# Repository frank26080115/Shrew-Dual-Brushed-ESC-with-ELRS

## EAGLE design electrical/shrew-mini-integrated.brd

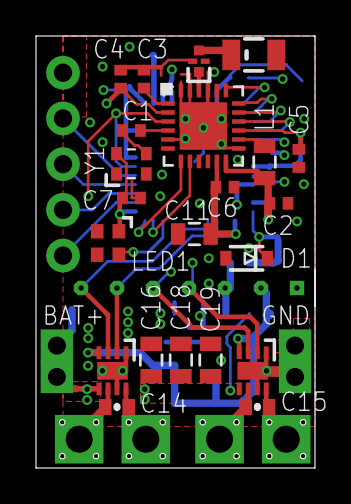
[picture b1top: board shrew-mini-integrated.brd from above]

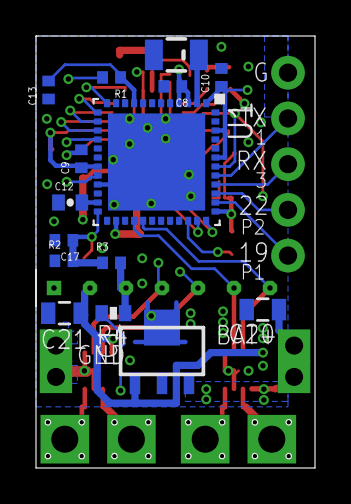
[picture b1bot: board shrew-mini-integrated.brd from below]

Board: 4 copper layers, 15.5 x 24.0 mm, 47 parts (15 on the bottom side), 35 nets.

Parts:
ANT1, ANT2: 74889302450; ANTENNA-CHIP2
C1: 1n; 0402-REV
C2, C13, C17: 470n; 0402-REV
C3, C4: 10n; 0402-REV
C5, C6, C7, C8, C9, C10: 100n; 0402-REV
C11: 10uF 25V; 0805
C12: DNP; 0402-CAP
C14, C15: 0402-CAP
C16, C18, C19, C20, C21: 0805
D1: 3V6; SOD-323
EDGE1: 1X05
FL1: 2450FM07D0034T; FIL_2450FM07D0034T
IC1: Vreg +3V3; SOT89
JP1: 1X07-2MM-TH-TINY
L1: 15u; 0805
LED1: SK6812-EC20
R1, R2, R3: 10K; 0402-REV
R4: 0402-RES
U1: ESP32-PICO-D4; PQFN50P700X700X104-49N
U2: SX1280IMLTRT; QFN24_4X4_SEM
U3, U4: DRV8231DSGR; WSON8_DRV8231_TEX
X1, X2, X3, X4: PIN-1X-BIG; PAD-1X-BIG
X5, X6, X7, X8: PIN-1X-MED; PAD-1X-MED
Y1: 52MHz TCXO; OSC_TG2016SMN_50.0000M-ECGNNMB

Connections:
3.3V: C5.2, C6.2, C7.2, C8.1, C9.1, C10.1, C11.1, C21.1, IC1.1, JP1.2, LED1.1, R1.2, U1.1, U1.3, U1.4, U1.19, U1.26, U1.37, U1.43, U1.46, U2.11, U2.15, U3.4, U4.4, Y1.4
+24V: C16.1, C18.1, C19.1, C20.1, IC1.3, R4.2, U3.5, U4.5, X5.1, X7.1
AUX1: EDGE1.1, U1.38
AUX2: EDGE1.2, U1.39
BATT-ADC: C17.1, D1.1, R2.2, R3.1, U1.24
ESP-BOOT: C12.2, U1.23
ESP-EN: C13.2, R1.1, U1.9
GND: C2.1, C3.1, C4.1, C5.1, C6.1, C7.1, C8.2, C9.2, C10.2, C11.2, C12.1, C13.1, C16.2, C17.2, C18.2, C19.2, C20.2, C21.2, D1.2, EDGE1.5, FL1.2, FL1.4, IC1.2, IC1.4, JP1.1, LED1.3, R2.1, U1.21, U1.49, U2.5, U2.13, U2.20, U2.21, U2.23, U2.24, U2.25, U3.1, U3.7, U3.9, U4.1, U4.7, U4.9, X6.1, X8.1, Y1.2
MOTOR1: C15.2, U4.6, X3.1
MOTOR2: C15.1, U4.8, X4.1
MOTOR3: C14.2, U3.6, X1.1
MOTOR4: C14.1, U3.8, X2.1
unnamed: ANT1.FEED, U1.2
unnamed: C1.1, Y1.3
unnamed: C1.2, U2.4
unnamed: FL1.1, U2.22
unnamed: ANT2.FEED, FL1.3
unnamed: L1.2, U2.14
unnamed: C3.2, U2.1
RADIO-BUSY: U1.36, U2.7
RADIO-CS: U1.12, U2.19
RADIO-DIO: U1.35, U2.8
RADIO-RST: U1.42, U2.3
RADIO-VDD: C2.2, C4.2, L1.1, U2.2, U2.12
RGBLED: LED1.4, U1.34
SIG1: JP1.4, U1.20, U4.2
SIG2: JP1.5, U1.16, U4.3
SIG3: JP1.6, U1.28, U3.2
SIG4: JP1.7, U1.29, U3.3
SPI-MISO: U1.15, U2.16
SPI-MOSI: U1.14, U2.17
SPI-SCK: U1.13, U2.18
U0RXD: EDGE1.3, U1.40
U0TXD: EDGE1.4, U1.41
V-ADC: JP1.3, R3.2, R4.1

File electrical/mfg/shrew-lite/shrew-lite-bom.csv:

Comment,Designator,Footprint,LCSC Part #
68K,R4,0402-RES,
1n,C1,0402-REV,
3V6 zener,D1,SOD-323,C306657
10K,R1 R2 R3,0402-REV,
10n,C3 C4,0402-REV,
10u,C11 C16 C18 C19 C20 C21,0805,C2932476
15u,L1,0805,C486333
X1G0054410320,Y1,OSC_TG2016SMN_50.0000M-ECGNNMB,C7503930
100n,C5 C6 C7 C8 C9 C10 C14 C15,0402-CAP,C1581
470n,C2 C13 C17,0402-REV,
2450FM07D0034T,FL1,FIL_2450FM07D0034T,C6054595
74889302450,ANT1 ANT2,ANTENNA-CHIP2,C6828492
DRV8231DSGR,U3 U4,WSON8_DRV8231_TEX,C5139865
ESP32-PICO-D4,U1,PQFN50P700X700X104-49N,C193707
SK6812-EC20,LED1,SK6812-EC20,C2909058
SX1280IMLTRT,U2,QFN24_4X4_SEM,C125969
DS8242-33A3L,IC1,SOT89,C5884130

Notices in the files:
parts and their libraries:
COPYRIGHT: Copyright (C) 2024 Ultra Librarian. All rights reserved.
